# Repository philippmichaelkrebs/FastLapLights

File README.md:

# FastLapLights

**"Gentlemen, start your engines!"** 🏁  

Bring FIA-style lighting to your slot car track with FastLapLights - a high-tech lighting and telemetry system for Carrera Digital tracks! 
Control WS2812b Start Lights, Pit Lane Lights and Track Flags with stunning LED animations that bring your races to life. Want more? FastLapLights als taps into the real-time data stream from the Carrera Control Unit, filters the most relevant messages, and outputs the via UART - perfect for powering external displays, mechanical 7-segment scoring pylons, or even fuel and pit-stop management systems. 
With support for 3.3V and 5V output, you've got everything you need to bring custom hardware into the mix.
Whether you're racing for fun or building the ultimate home track, FastLapLights adds a whole new level of immersion, control and creativity.

Following Models are supported:
- Carrera Digital 124
- Carrera Digital 132

Preview:  

# Features

## Start Lights
Perfect race countdown sequence with WS2812B LEDs 🚦

You can switch between horizontal and vertical alignment for the start lights WS2812B led strips. Vertical alignment requires more soldering but looks more realistic, giving you the option to physically seperate the  lights - just like in real motorsport.
The system is designed to handle 40 leds. So both the front and the back of the lights illuminated. You nearly have a 360 degree visibility of the start lights.

## Pit Lane Lights
Manage pit stops like a real motorsport pro!

Instead of start loghts, you can choose to illuminate pit lane lights. This is an either-or option - controlled via a solder bridge on the back of the pcb. Simpy close the appropriate bridge to switch the functionality.

## Track Flag System
RGB LEDs indicate race conditions (Green, Yellow, Red) 🚥

With a red and green led, you can animate track lights. It's also possible to use a rgb led with r and g connected only. Race status indicated by flags:
- Green: go, 
- Yellow: caution, 
- Red: stop
If you plan to use multiple RGB LEDs, you should use a mosfet to avoid overloading the uCs GPIOs.

## Real-Time Data Capture
Tap into live control unit telemetry!

The STM32 continuously processes data from the Carrera Control Unit. A filtered stream of the most relevant messages is available via the UART interface. This gives you a powerful foundation to build custom applications and add unique behavior to your racetrack setup. 
Whether it's a mechanical 7-segment scoring pylon or a smart pit stop prediction system, FastLapLights gives your cicuit the edge it deserves.

# Get Started

- Order the microcontroller from jlcpcb (see section documentation)
- Flash the firmware on your STM32 microcontroller (see section documentation)
- Connect WS2812B & RGB LEDs according to the purpose.
- Solder power wires to the track
- Power up & lights out!

# Pinouts

# UART
The data that is transmitted by the Control Unit is an asynchronous serial protocol. The chunks are of various size. Notably, the protocol doesn't use a traditional stop bit. The cu transmits data in a structured, continouos stream every 75 milli secs. Each transmission cycle contains 10 distinct messages sent in a strict and predictable sequence.

The controller processes this incomimg data and outputs it via UART, using a **32-byte single-buffered TX DMA system**. Each UART transmission contains a snapshot of the current race state. TX only, RX is disabled.

## UART Configuration
- Baud rate: 115200
- Data format: 8 data bits, no parity, 1 stop bit (8N1)
## Application Behavior
- Message Size: Each UART message is exactly 32 bytes in length.
- Contents: The message includes all relevant application data (e.g., race state, positions, fuel levels, etc.) and is a snapshot of the current race state.
- Transmission Rate: A new message is transmitted every 750 milliseconds.

|Byte Index|Field|Description|
|---|---|---|
|{0,4,...}|`Driver X - Fuel`|Remaining fuel of Driver 0–5|
|{1,5,...}|`Driver X - Position`|Current position of Driver 0–5|
|{2,6,...}|`Driver X - Finished`|Driver 0–5 has finished the race (1 = finished)|
|{3,7,...}|`Driver X - Laps`|Laps completed by Driver 0–5|
|24|`Fastest Lap`|Driver index with the fastest lap (0–5, or 0xFF if none)|
|25|`Start Lights Count`|Number of red lights currently lit|
|26|`Lap Count`|Total laps completed by the leader|
|27|`Reset Event`|Non-zero if a global reset has occurred|
|28|`Race State`|Current state of the race (see `RaceState` enum)|
|29|`Session Type`|Race or Qualifying session (see `SessionType` enum)|
|30 & 31|`Track Time`|16-bit track time counter, synced with track (13.33 Hz)|

## Message Decoding Example

The following C code snippet demonstrates how to decode the message and populate internal state structures:
```c 
typedef enum {
	RACE,
	QUALIFYING_TRAINING
}S essionType;

typedef enum {
	RACE_STATE_STARTUP,
	RACE_STATE_RED_FLAG,
	RACE_STATE_YELLOW_FLAG,
	RACE_STATE_GREEN_FLAG,
	RACE_STATE_START_PROC,
	RACE_STATE_JUMP_START,
	RACE_STATE_OPEN
} RaceState;

typedef struct {
	uint8_t fuel;
	uint8_t position;
	uint8_t finished;
	uint8_t laps;
} DriverData;

typedef struct {
	DriverData 	      driver_data[6];
	uint8_t		fastest_lap_driver;
	uint8_t		start_lights;
	uint8_t		lap_count;
	uint8_t		lap_count_nibble_completed;
	uint8_t		reset_event;
	RaceState	      race_state;
	SessionType	      session_type;
} RaceInfo;

// Global structure updated via UART
volatile RaceInfo	uart_race_info = {
		.driver_data = {
			{ .fuel = 0, .position = 0, .finished = 0, .laps = 0 },
			{ .fuel = 0, .position = 0, .finished = 0, .laps = 0 },
			{ .fuel = 0, .position = 0, .finished = 0, .laps = 0 },
			{ .fuel = 0, .position = 0, .finished = 0, .laps = 0 },
			{ .fuel = 0, .position = 0, .finished = 0, .laps = 0 },
			{ .fuel = 0, .position = 0, .finished = 0, .laps = 0 }
		},
		.fastest_lap_driver = 0xFF,       // 0xFF no fastest lap yet
		.start_lights = 0,
		.lap_count = 0,
		.reset_event = 0,
		.race_state = RACE_STATE_STARTUP,
		.session_type = RACE
	};
	
volatile uint8_t rx_buf[32];

void uart_interrupt(void){
	uint8_t buf_idx = 0;
	for (uint8_t _driver = 0; _driver < 6; _driver++){
		uart_race_info.driver_data[_driver].position = 
			rx_buf[buf_idx++];
		uart_race_info.driver_data[_driver].fuel = 
			rx_buf[buf_idx++];
		uart_race_info.driver_data[_driver].laps = 
			rx_buf[buf_idx++];
		uart_race_info.driver_data[_driver].finished = 
			rx_buf[buf_idx++];
	}

	uart_race_info.fastest_lap_driver = rx_buf[buf_idx++];
	uart_race_info.start_lights = rx_buf[buf_idx++];
	uart_race_info.lap_count = rx_buf[buf_idx++];
	uart_race_info.reset_event = rx_buf[buf_idx++];
	uart_race_info.race_state = (RaceState)rx_buf[buf_idx++];
	uart_race_info.session_type = (SessionType)rx_buf[buf_idx++];

	track_time = 0xFF00 & (rx_buf[buf_idx++] << 8);
	track_time |= rx_buf[buf_idx++];
}
```

# Documentation
- [How the Lights Work](/docs/how_the_lights_work.md)
- [Getting Started](/docs/getting_started.md)

# Contribute & Support

Got ideas? Found a bug? Want to make it even cooler? 
Open an issue, submit a PR, or just say hi!

Developer: Philipp Krebs  
Contact: pmge.krebs@gmail.com  
Repo: https://github.com/philippmichaelkrebs

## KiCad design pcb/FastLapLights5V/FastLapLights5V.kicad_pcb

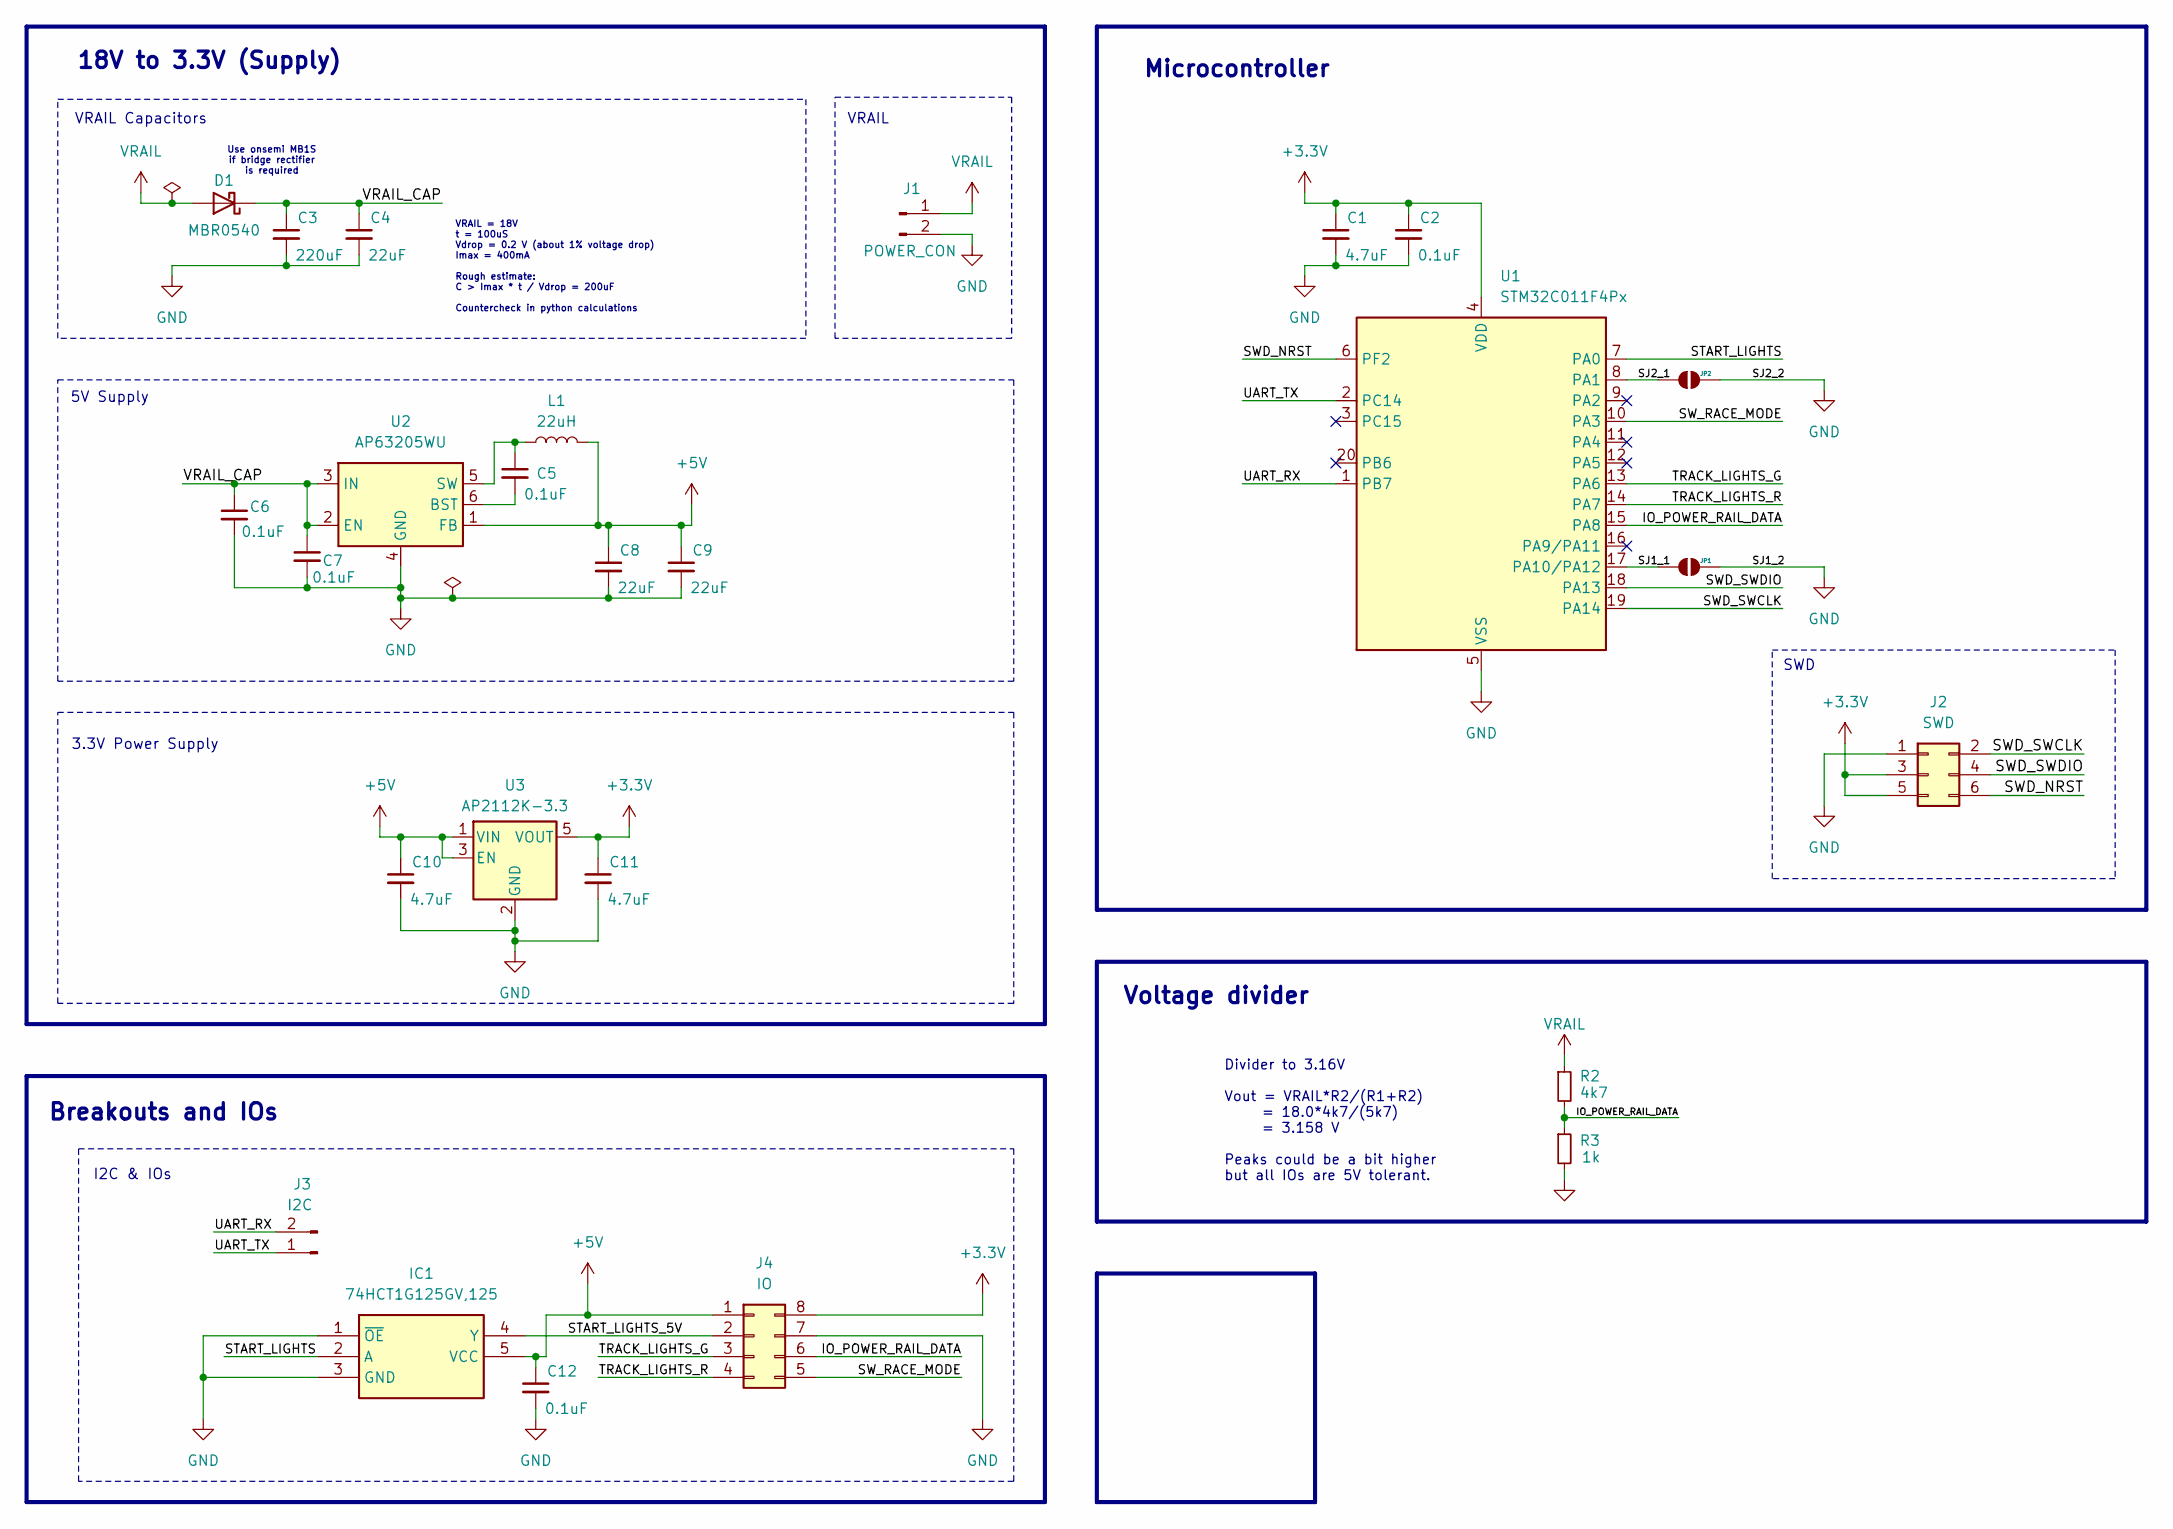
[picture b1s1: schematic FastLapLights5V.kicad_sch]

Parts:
C1, C10, C11: 4.7uF; C_0603_1608Metric; LCSC C1705
C2, C5, C6, C7, C12: 0.1uF; C_0603_1608Metric; LCSC C1591
C3: 220uF; CP_220_Honor_Elec_HV1E227M0810PZ; LCSC C5246542
C4: 22uF; C_0805_2012Metric; LCSC C602037
C8, C9: 22uF; C_0603_1608Metric; LCSC C86295
D1: MBR0540; D_SOD-123; LCSC C236080
IC1: 74HCT1G125GV,125; SOT95P275X110-5N; Mouser Part Number 771-74HCT1G125GV
J1: POWER_CON; PinHeader_2x01_P2.54mm_Vertical
J2: SWD; PinHeader_2x03_P2.54mm_Vertical
J3: I2C; PinHeader_1x02_P2.54mm_Vertical
J4: IO; PinHeader_2x04_P2.54mm_Vertical
JP1, JP2: SP; SolderJumper-2_P1.3mm_Open_RoundedPad1.0x1.5mm
L1: 22uH; L_SXN_SMDRH104R-220MT; LCSC C72414
R2: 4k7; R_0603_1608Metric; LCSC C99782
R3: 1k; R_0603_1608Metric; LCSC C22548
U1: STM32C011F4Px; TSSOP-20_4.4x6.5mm_P0.65mm; LCSC C5452432
U2: AP63205WU; TSOT-23-6; LCSC C2071056
U3: AP2112K-3.3; SOT-23-5; LCSC C3021085

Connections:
+3.3V: C1.1, C2.1, C11.1, J2.3, J2.5, J4.8, U1.4 (VDD), U3.5 (VOUT)
+5V: C8.1, C9.1, C10.1, C12.1, IC1.5 (VCC), J4.1, L1.2, U2.1 (FB), U3.1 (VIN), U3.3 (EN)
/IO_POWER_RAIL_DATA: J4.6, R2.2, R3.1, U1.15 (PA8)
/SJ1_1: JP1.1 (A), U1.17 (PA10/PA12)
/SJ2_1: JP2.1 (A), U1.8 (PA1)
/START_LIGHTS: IC1.2 (A), U1.7 (PA0)
/START_LIGHTS_5V: IC1.4 (Y), J4.2
/SWD_NRST: J2.6, U1.6 (PF2)
/SWD_SWCLK: J2.2, U1.19 (PA14)
/SWD_SWDIO: J2.4, U1.18 (PA13)
/SW_RACE_MODE: J4.5, U1.10 (PA3)
/TRACK_LIGHTS_G: J4.3, U1.13 (PA6)
/TRACK_LIGHTS_R: J4.4, U1.14 (PA7)
/UART_RX: J3.2, U1.1 (PB7)
/UART_TX: J3.1, U1.2 (PC14)
/VRAIL_CAP: C3.1, C4.1, C6.1, C7.1, D1.1 (K), U2.2 (EN), U2.3 (IN)
GND: C1.2, C2.2, C3.2, C4.2, C6.2, C7.2, C8.2, C9.2, C10.2, C11.2, C12.2, IC1.1 (~OE), IC1.3 (GND), J1.2, J2.1, J4.7, JP1.2 (B), JP2.2 (B), R3.2, U1.5 (VSS), U2.4 (GND), U3.2 (GND)
unnamed: C5.2, U2.6 (BST)
unnamed: C5.1, L1.1, U2.5 (SW)
VRAIL: D1.2 (A), J1.1, R2.1

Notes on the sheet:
3.3V Power Supply
Use onsemi MB1S if bridge rectifier is required
5V Supply
Voltage divider
Breakouts and IOs
Microcontroller
Divider to 3.16V Vout = VRAIL*R2/(R1+R2) = 18.0*4k7/(5k7) = 3.158 V Peaks could be a bit higher but all IOs are 5V tolerant.
VRAIL = 18V t = 100uS Vdrop = 0.2 V (about 1% voltage drop) Imax = 400mA Rough estimate: C > Imax * t / Vdrop = 200uF Countercheck in python calculations
VRAIL
SWD
VRAIL Capacitors
I2C & IOs
18V to 3.3V (Supply)

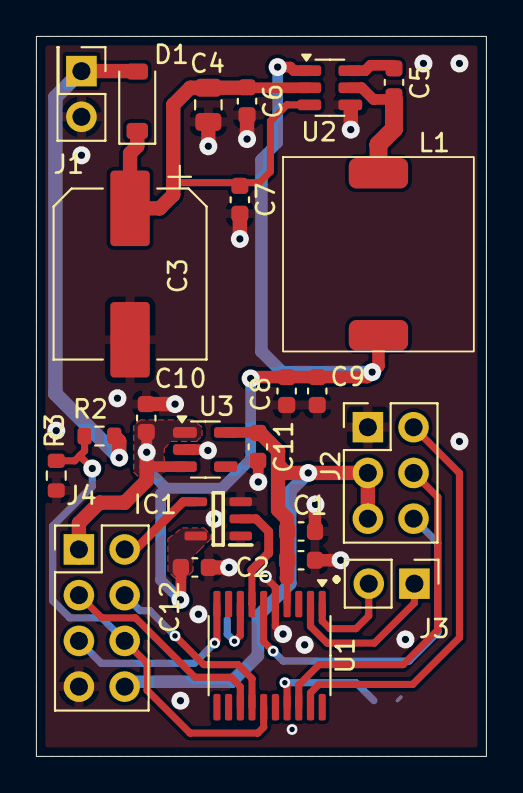
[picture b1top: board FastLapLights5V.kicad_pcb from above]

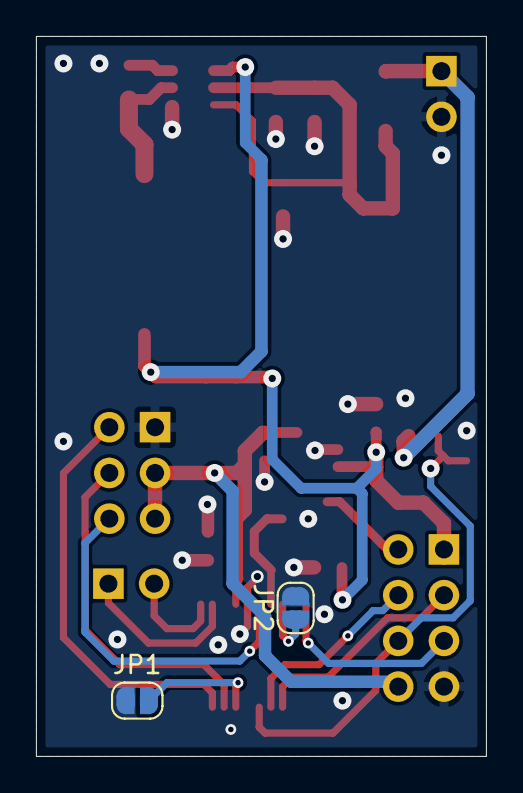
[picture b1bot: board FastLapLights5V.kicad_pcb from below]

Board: 4 copper layers, 25.0 x 40.0 mm, 26 parts (2 on the bottom side), 20 nets.

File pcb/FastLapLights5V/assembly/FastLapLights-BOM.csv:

"Designator","Comment","Footprint","LCSC"
"C1,C10,C11","4.7uF","Capacitor_SMD:C_0603_1608Metric"," C1705"
"C2,C5,C6,C7,C12","0.1uF","Capacitor_SMD:C_0603_1608Metric","C1591"
"C3","220uF","Library:CP_220_Honor_Elec_HV1E227M0810PZ","C5246542"
"C4","22uF","Capacitor_SMD:C_0805_2012Metric","C602037"
"C8,C9","22uF","Capacitor_SMD:C_0603_1608Metric"," C86295"
"D1","MBR0540","Diode_SMD:D_SOD-123","C236080"
"IC1","74HCT1G125GV,125","Library:SOT95P275X110-5N","C12502"
"L1","22uH","Library:L_SXN_SMDRH104R-220MT","C72414"
"R2","4k7","Resistor_SMD:R_0603_1608Metric","C99782"
"R3","1k","Resistor_SMD:R_0603_1608Metric","C22548"
"U1","STM32C011F4Px","Package_SO:TSSOP-20_4.4x6.5mm_P0.65mm","C5452432"
"U2","AP63205WU","Package_TO_SOT_SMD:TSOT-23-6","C2071056"
"U3","AP2112K-3.3","Package_TO_SOT_SMD:SOT-23-5","C3021085"

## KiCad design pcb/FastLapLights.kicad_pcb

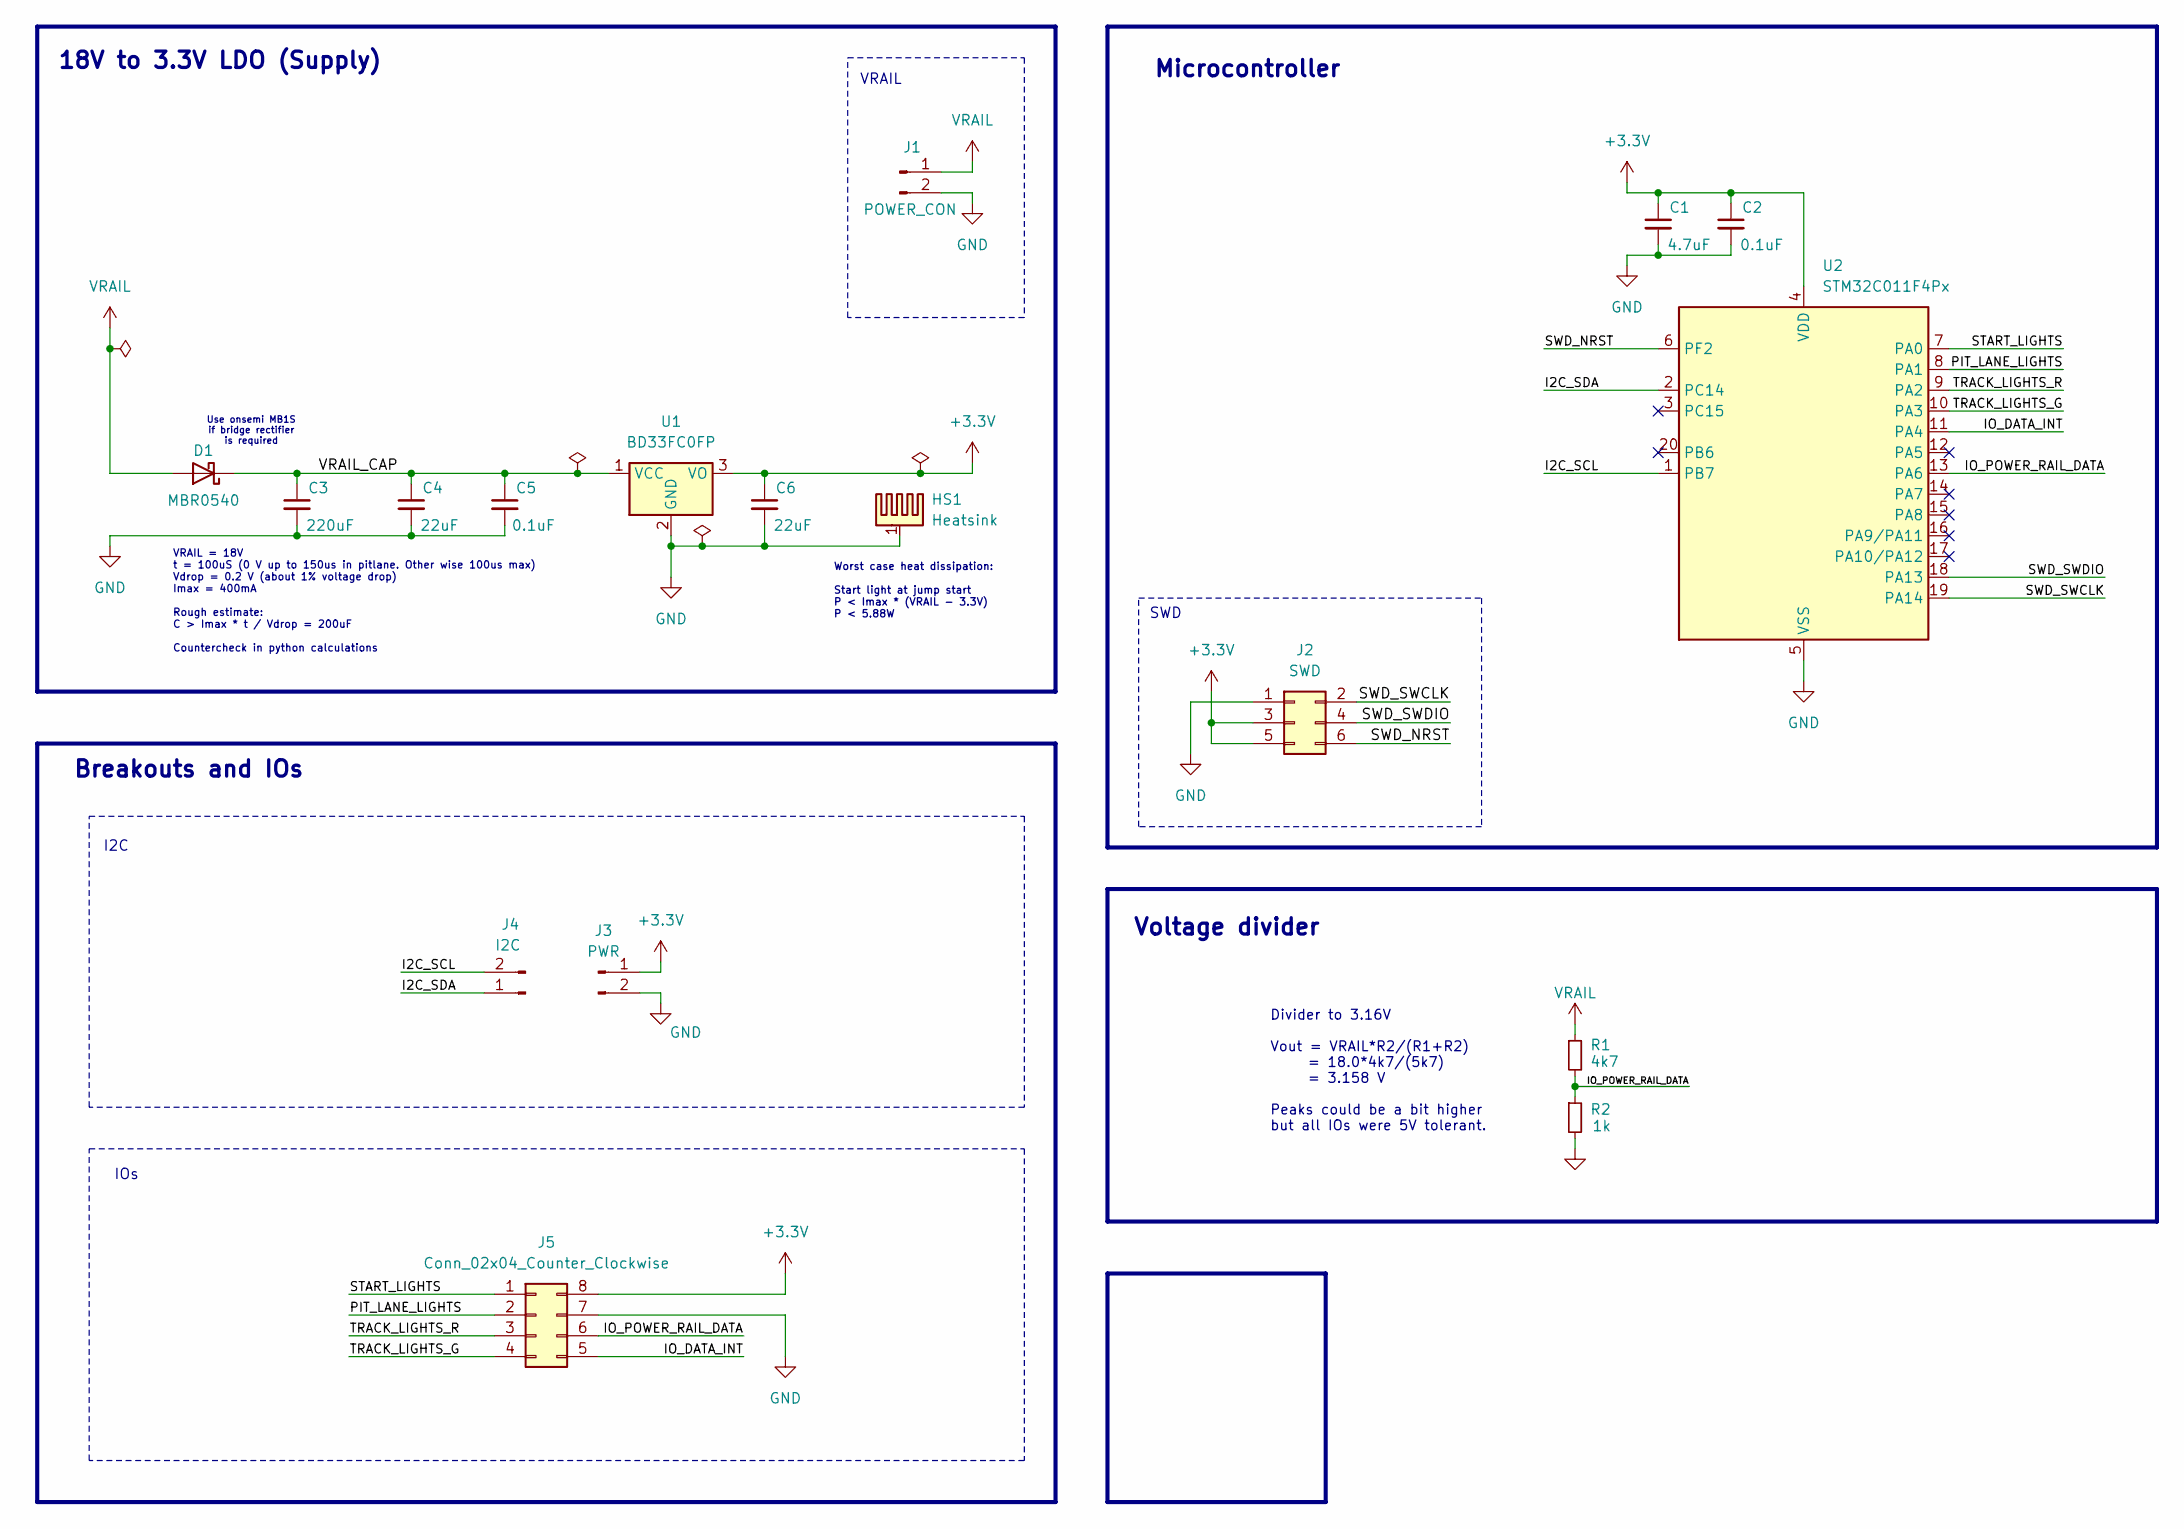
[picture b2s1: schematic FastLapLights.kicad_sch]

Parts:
C1: 4.7uF; C_0603_1608Metric; LCSC C1705
C2: 0.1uF; C_0603_1608Metric; LCSC C1591
C3: 220uF; CP_Elec_A768KS227M1VLAE024; LCSC C3274444
C4: 22uF; C_0805_2012Metric; LCSC C602037
C5: 0.1uF; C_0805_2012Metric; LCSC C519981
C6: 22uF; C_0603_1608Metric; LCSC C86295
D1: MBR0540; D_SOD-123; LCSC C236080
HS1: Heatsink; Heatsink_DV-T263-201E-TR
J1: POWER_CON; PinHeader_2x01_P2.54mm_Vertical
J2: SWD; PinHeader_2x03_P2.54mm_Vertical
J3: PWR; PinHeader_1x02_P2.54mm_Vertical
J4: I2C; PinHeader_1x02_P2.54mm_Vertical
J5: Conn_02x04_Counter_Clockwise; PinHeader_2x04_P2.54mm_Vertical
R1: 4k7; R_0603_1608Metric; LCSC C99782
R2: 1k; R_0603_1608Metric; LCSC C22548
U1: BD33FC0FP; TO-252-2; LCSC C5336749
U2: STM32C011F4Px; TSSOP-20_4.4x6.5mm_P0.65mm; LCSC C5452432

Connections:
+3.3V: C1.1, C2.1, C6.1, J2.3, J2.5, J3.1, J5.8, U1.3 (VO), U2.4 (VDD)
/I2C_SCL: J4.2, U2.1 (PB7)
/I2C_SDA: J4.1, U2.2 (PC14)
/IO_DATA_INT: J5.5, U2.11 (PA4)
/IO_POWER_RAIL_DATA: J5.6, R1.2, R2.1, U2.13 (PA6)
/PIT_LANE_LIGHTS: J5.2, U2.8 (PA1)
/START_LIGHTS: J5.1, U2.7 (PA0)
/SWD_NRST: J2.6, U2.6 (PF2)
/SWD_SWCLK: J2.2, U2.19 (PA14)
/SWD_SWDIO: J2.4, U2.18 (PA13)
/TRACK_LIGHTS_G: J5.4, U2.10 (PA3)
/TRACK_LIGHTS_R: J5.3, U2.9 (PA2)
/VRAIL_CAP: C3.1, C4.1, C5.1, D1.1 (K), U1.1 (VCC)
GND: C1.2, C2.2, C3.2, C4.2, C5.2, C6.2, HS1.1, J1.2, J2.1, J3.2, J5.7, R2.2, U1.2 (GND), U2.5 (VSS)
VRAIL: D1.2 (A), J1.1, R1.1

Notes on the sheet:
Use onsemi MB1S if bridge rectifier is required
Voltage divider
Breakouts and IOs
Microcontroller
Divider to 3.16V Vout = VRAIL*R2/(R1+R2) = 18.0*4k7/(5k7) = 3.158 V Peaks could be a bit higher but all IOs were 5V tolerant.
VRAIL = 18V t = 100uS (0 V up to 150us in pitlane. Other wise 100us max) Vdrop = 0.2 V (about 1% voltage drop) Imax = 400mA Rough estimate: C > Imax * t / Vdrop = 200uF Countercheck in python calculations
VRAIL
Worst case heat dissipation: Start light at jump start P < Imax * (VRAIL - 3.3V) P < 5.88W
SWD
IOs
I2C
18V to 3.3V LDO (Supply)

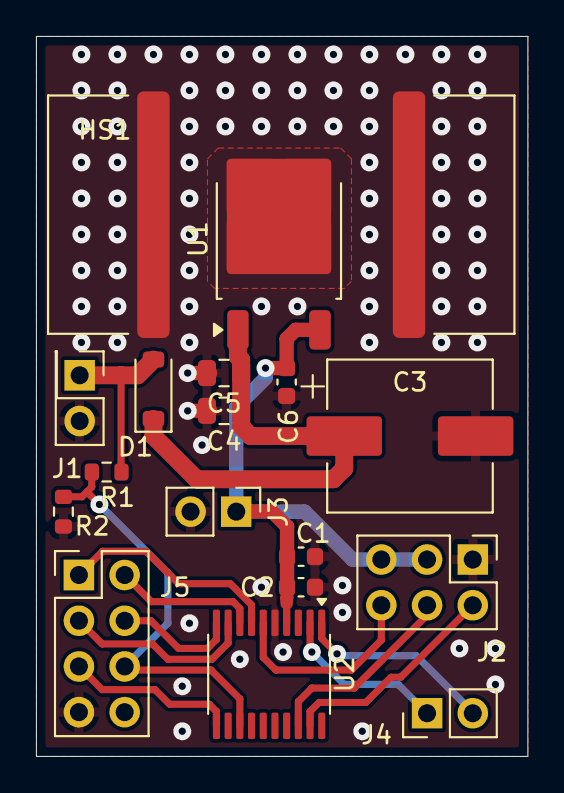
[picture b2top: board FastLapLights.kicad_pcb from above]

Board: 4 copper layers, 27.3 x 40.0 mm, 17 parts (0 on the bottom side), 15 nets.

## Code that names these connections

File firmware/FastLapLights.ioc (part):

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Mcu.Name=STM32C011F(4-6)Px
Mcu.Package=TSSOP20
Mcu.UserName=STM32C011F4Px
PA0.GPIOParameters=GPIO_Speed
PA0.GPIO_Speed=GPIO_SPEED_FREQ_HIGH
PA0.Signal=S_TIM16_CH1
PA1.GPIOParameters=GPIO_PuPd,GPIO_Label
PA1.GPIO_Label=START_LIGHT_ALIGNMENT
PA1.GPIO_PuPd=GPIO_PULLUP
PA1.Signal=GPIO_Input
PA12\ [PA10].GPIOParameters=GPIO_PuPd,GPIO_Label
PA12\ [PA10].GPIO_Label=LIGHT_MODE_SJ
PA12\ [PA10].GPIO_PuPd=GPIO_PULLUP
PA12\ [PA10].Signal=GPIO_Input
PA13.Mode=Serial_Wire
PA13.Signal=DEBUG_SWDIO
PA14-BOOT0.Mode=Serial_Wire
PA14-BOOT0.Signal=DEBUG_SWCLK
PA3.GPIOParameters=GPIO_PuPd,GPIO_Label
PA3.GPIO_Label=RACE_TRAINING_SESSION_SW
PA3.GPIO_PuPd=GPIO_PULLUP
PA3.Signal=GPIO_Input
PA6.GPIOParameters=GPIO_Label
PA6.GPIO_Label=TRACK_GREEN
PA6.Signal=GPIO_Output
PA7.GPIOParameters=GPIO_Label
PA7.GPIO_Label=TRACK_RED_PWM
PA7.Signal=S_TIM14_CH1
PA8.GPIOParameters=GPIO_Label
PA8.GPIO_Label=IO_POWER_RAIL_DATA_FALL
PA8.Signal=S_TIM3_CH4
PB7.GPIOParameters=GPIO_ModeDefaultPP,GPIO_PuPd
PB7.GPIO_ModeDefaultPP=GPIO_MODE_AF_PP
PB7.GPIO_PuPd=GPIO_PULLUP
PB7.Mode=Asynchronous
PB7.Signal=USART1_RX
PC14-OSCX_IN\ (PC14).GPIOParameters=GPIO_ModeDefaultPP
PC14-OSCX_IN\ (PC14).GPIO_ModeDefaultPP=GPIO_MODE_AF_PP
PC14-OSCX_IN\ (PC14).Mode=Asynchronous
PC14-OSCX_IN\ (PC14).Signal=USART1_TX
RCC.HSE_VALUE=8000000
RCC.SYSCLKFreq_VALUE=48000000
board=custom

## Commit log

2025-03-27 clean, move, refactor
2025-03-27 remove invalid ssh h files that have crept in
2025-03-28 add pcb mk4 remake
2025-03-28 assembly files
2025-03-28 add grb
2025-03-28 update footprint
2025-03-28 alter readme
2025-04-02 prep firmware
2025-04-03 migrate ws2812b and manchester decoder
2025-04-04 tried to fix stubborn hal
2025-04-05 fix bad behavior of first led - omg what a hair-raising solution. Let the dma catch breath before sending the first bit
2025-04-06 migrate states
2025-04-07 migrate track lights
2025-04-07 add some pics
2025-04-07 remove some pics
2025-04-07 migrate some docs. More to do
2025-04-10 add light behavior
2025-04-11 add gifs
2025-04-11 doc light behavior update
2025-04-11 doc links in readme leads to 404
2025-04-13 add 5V version
2025-04-14 change jlcpcb parts
2025-04-14 change sj start light - pit lane light
2025-05-14 fix issues with decoding manchester data and make it more reliable
2025-05-15 activate solder jumper pin, replace sold-out components
2025-06-11 - add race mode practice session - i2c to uart for faster datastreaming to displays - fix timer issue with tim1
2025-07-04 make usart work again
2025-07-08 change to readme
2025-07-16 add wiring
2025-07-16 add horizontal vertical scheme
2025-10-13 - save some spave with ll driver - rewrite data link layer :cq git commit -m
2026-01-01 firmware - reduce text size
2026-01-01 modify license
2026-01-10 fix workaround
2026-03-10 Add German translations and enhance README content
    Updated the README to include German translations and improved descriptions of features and functionalities.
2026-03-10 Revise README for improved feature descriptions
    Updated README.md to enhance clarity and detail about FastLapLights features and usage.
